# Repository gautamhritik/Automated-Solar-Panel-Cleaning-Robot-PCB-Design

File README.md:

# Automated Solar Panel Cleaning Robot – PCB Design

## Overview
This repository contains the custom PCB design for an Automated Solar Panel Cleaning Robot.  
The PCB integrates power management, motor interfacing, sensor inputs, communication protocols and system protection required for autonomous solar panel cleaning.

This project is intended for academic, prototyping, and learning purposes.

## Key Features
- Battery-powered operation with regulated outputs
- Buck converter for 5 V and 3.3 V rails
- Motor driver interface for the cleaning mechanism
- Sensor input support (0–3.3 V range)
- Power switch and LED status indication
- Reverse polarity, overcurrent, and transient protection
- Debug and expansion headers

## PCB Specifications
- Design Tool: KiCad
- PCB Layers: 2
- Input Power: Battery / External DC supply
- Logic Levels: 3.3 V, 5 V
- Design Status: Prototype (ERC & DRC verified)
- 
## Usage
1. Open schematic and PCB files using KiCad
2. Review power paths, connectors, and component ratings
3. Modify the design if required
4. Generate Gerber files for fabrication
5. Assemble and test the PCB

## Limitations
- Prototype and academic use only
- Not weatherproof or industrially certified
- Requires enclosure for real-world deployment

## Future Improvements
- EMI and noise optimization
- Battery monitoring and protection enhancement
- Waterproof connectors and enclosure
- Firmware-based diagnostics

## License
MIT License

## Author
Hritik Gautam

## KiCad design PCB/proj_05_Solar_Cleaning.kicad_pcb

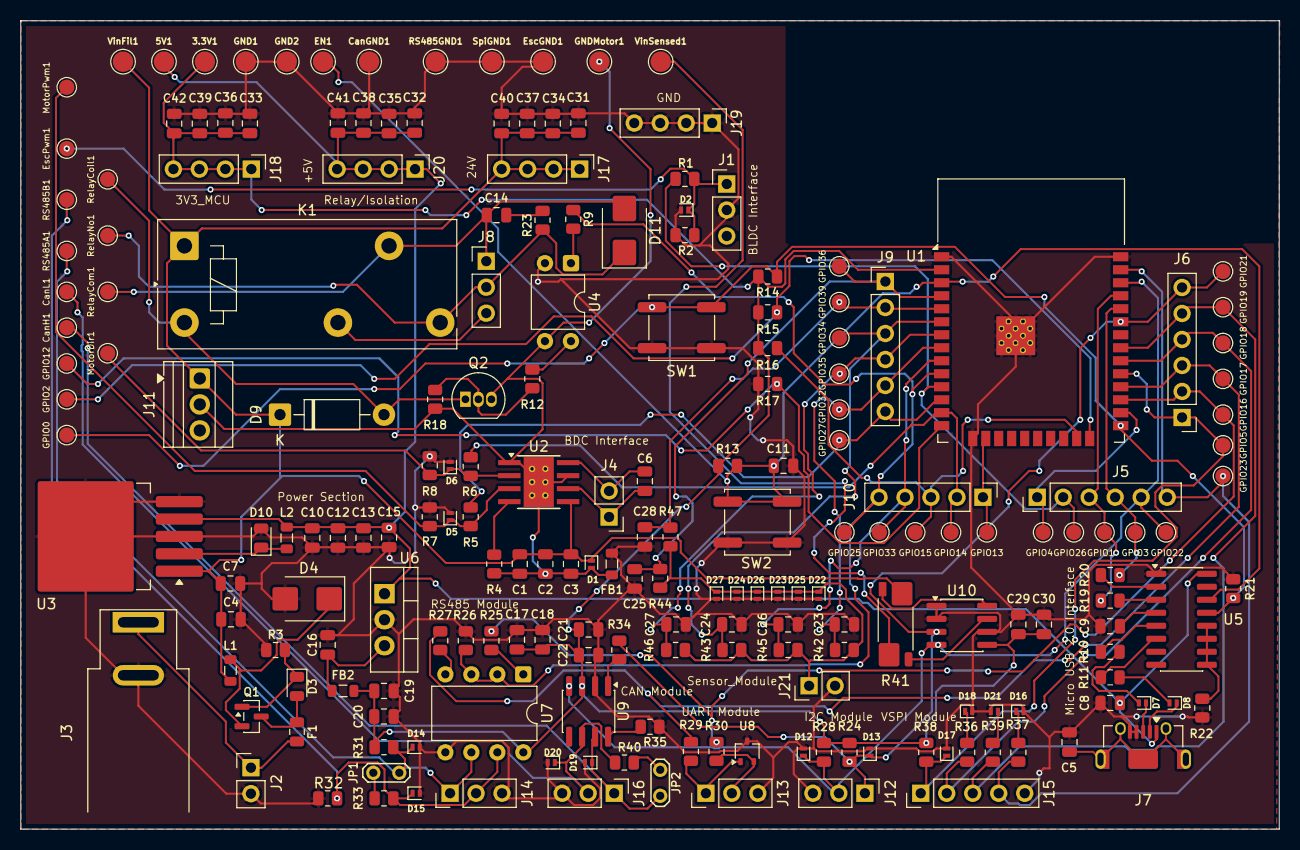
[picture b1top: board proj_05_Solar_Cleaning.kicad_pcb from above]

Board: 2 copper layers, 123.0 x 79.0 mm, 207 parts (0 on the bottom side), 82 nets.

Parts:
3.3V1, 5V1: TestPoint; TestPoint_Pad_D2.0mm
C1: 500µF; C_0805_2012Metric
C2, C5, C6, C9, C11, C13, C17, C20, C21, C23, C24, C25, C26, C27, C28, C29, C37, C38, C39, C40, C41, C42: 0.1µF; C_0805_2012Metric
C3, C12, C18, C19, C22, C30, C34, C35, C36: 1µF; C_0805_2012Metric
C4: C; C_0805_2012Metric
C7, C10: 100µF; C_0805_2012Metric
C8, C15, C31, C32, C33: 10µF; C_0805_2012Metric
C14: 100nF; C_0805_2012Metric
C16: 22µF; C_0805_2012Metric
CanGND1: TestPoint; TestPoint_Pad_D2.0mm
CanH1: TestPoint; TestPoint_Pad_D1.5mm
CanL1: TestPoint; TestPoint_Pad_D1.5mm
D1, D2, D5, D6, D7, D8, D12, D13, D14, D15, D16, D17, D18, D19, D20, D21, D22, D23, D24, D25, D26, D27: PESD5V0L1UL; D_SOD-882
D3: D_Zener; D_0805_2012Metric
D4, D11: D_TVS; D_SMB
D9: 1N4007; D_DO-41_SOD81_P10.16mm_Horizontal
D10: D_Schottky; D_0805_2012Metric
EN1: TestPoint; TestPoint_Pad_D2.0mm
EscGND1: TestPoint; TestPoint_Pad_D2.0mm
EscPwm1: TestPoint; TestPoint_Pad_D1.5mm
F1: Fuse; Fuse_0805_2012Metric
FB1, FB2: FerriteBead; L_0805_2012Metric
GND1, GND2: TestPoint; TestPoint_Pad_D2.0mm
GNDMotor1: TestPoint; TestPoint_Pad_D2.0mm
GPIO0, GPIO1, GPIO2, GPIO3, GPIO4, GPIO5, GPIO12, GPIO13, GPIO14, GPIO15, GPIO16, GPIO17, GPIO18, GPIO19, GPIO21, GPIO22, GPIO23, GPIO25, GPIO26, GPIO27, GPIO32, GPIO33, GPIO34, GPIO35, GPIO36, GPIO39: TestPoint; TestPoint_Pad_D1.5mm
J1, J8, J12, J13, J14, J16: Conn_01x03_Pin; PinHeader_1x03_P2.54mm_Vertical
J2, J4, J21: Conn_01x02_Pin; PinHeader_1x02_P2.54mm_Vertical
J3: Jack-DC; BarrelJack_SwitchcraftConxall_RAPC10U_Horizontal
J5, J6, J9: Conn_01x06_Pin; PinHeader_1x06_P2.54mm_Vertical
J7: USB_B_Micro; USB_Micro-AB_Molex_47590-0001
J10, J15: Conn_01x05_Pin; PinHeader_1x05_P2.54mm_Vertical
J11: Screw_Terminal_01x03; TerminalBlock_Xinya_XY308-2.54-3P_1x03_P2.54mm_Horizontal
J17, J18, J19, J20: Conn_01x04_Pin; PinHeader_1x04_P2.54mm_Vertical
JP1, JP2: Jumper_2_Open; TestPoint_2Pads_Pitch2.54mm_Drill0.8mm
K1: Relay_SPDT; Relay_SPDT_Finder_40.51
L1: L; L_0805_2012Metric
L2: 47µH; L_0805_2012Metric
MotorDir1: TestPoint; TestPoint_Pad_D1.5mm
MotorPwm1: TestPoint; TestPoint_Pad_D1.5mm
Q1: Q_PMOS_GDS; SOT-23
Q2: BC337; TO-92_Inline
R1, R5, R6, R19, R20, R23: 100; R_0805_2012Metric
R2, R7, R8: 100K; R_0805_2012Metric
R3, R13, R14, R15, R16, R17, R18, R21, R22, R26, R35: 10K; R_0805_2012Metric
R4: 22K; R_0805_2012Metric
R9, R31, R32: 680; R_0805_2012Metric
R10, R11: 22; R_0805_2012Metric
R12, R42, R43, R44, R45, R46, R47: 1K; R_0805_2012Metric
R24, R28: 4.7K; R_0805_2012Metric
R25, R27, R29, R30, R34: 33; R_0805_2012Metric
R33, R40: 120; R_0805_2012Metric
R36, R37, R39: 47; R_0805_2012Metric
R38: 47K; R_0805_2012Metric
R41: R_Shunt = 5 mΩ, ≥2 W, 2512package; R_Shunt_Vishay_WSK2512_6332Metric_T1.19mm
RS485A1, RS485B1: TestPoint; TestPoint_Pad_D1.5mm
RS485GND1: TestPoint; TestPoint_Pad_D2.0mm
RelayCoil1: TestPoint; TestPoint_Pad_D1.5mm
RelayCom1: TestPoint; TestPoint_Pad_D1.5mm
RelayNo1: TestPoint; TestPoint_Pad_D1.5mm
SW1, SW2: SW_Push; SW_Push_1P1T_NO_CK_KSC7xxJ
SpiGND1: TestPoint; TestPoint_Pad_D2.0mm
U1: ESP32-WROOM-32D
U2: DRV8871DDA; Texas_HTSOP-8-1EP_3.9x4.9mm_P1.27mm_EP2.95x4.9mm_Mask2.4x3.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
U3: LM2596S-5; TO-263-5_TabPin3
U4: PC817; DIP-4_W7.62mm
U5: CH340C; SOIC-16_3.9x9.9mm_P1.27mm
U6: MCP1825S; TO-220-3_Vertical
U7: MAX3485; DIP-8_W7.62mm
U8: TPD2E2U06DCK; SOT-323_SC-70
U9: SN65HVD230; SOIC-8_3.9x4.9mm_P1.27mm
U10: INA219AxD; SOIC-8_3.9x4.9mm_P1.27mm
VinFil1: TestPoint; TestPoint_Pad_D2.0mm
VinSensed1: TestPoint; TestPoint_Pad_D2.0mm

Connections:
/3V3: C16.1, FB2.1, U6.3 (VO)
/3V3_MCU: 3.3V1.1, C17.1, C18.1, C19.1, C20.1, C21.1, C22.1, C29.1, C30.1, C33.1, C36.1, C39.1, C42.1, FB2.2, J18.1, J18.2, J18.3, J18.4, R13.1, R14.2, R15.2, R16.2, R24.1, R28.1, R31.2, R38.2, U1.2 (VDD), U7.8 (VCC), U9.3 (VCC), U10.5 (VS)
/+5V: 5V1.1, C8.1, C10.1, C12.1, C13.1, C15.1, C32.1, C35.1, C38.1, C41.1, J7.1 (VBUS), J20.1, J20.2, J20.3, J20.4, L2.2, U3.4 (FB), U5.16 (VCC), U6.1 (VI)
/CANH: CanH1.1, D19.1 (K), J16.1, JP2.1 (A), U9.7 (CANH)
/CANL: CanL1.1, D20.1 (K), J16.2, R40.1, U9.6 (CANL)
/EN: C11.1, EN1.1, R13.2, SW2.2, U1.3 (EN), U5.14 (~RTS)
/ESC_PWM_OUT: D2.1 (K), EscPwm1.1, J1.1, R1.2, R2.2
/GND_MOTOR: C1.2, C2.2, C3.2, D1.2 (A), FB1.1, GNDMotor1.1, J11.2, Q2.3 (E), R4.1, R18.1, U2.1 (GND), U2.7 (GND), U2.9 (GND), U4.3
/GPIO0: GPIO0.1, R14.1, R21.2, SW1.1, U1.25 (IO0), U5.13 (~DTR)
/GPIO1: GPIO1.1, J5.3, R19.1, U1.35 (TXD0/IO1)
/GPIO2: GPIO2.1, R15.1, U1.24 (IO2)
/GPIO3: GPIO3.1, J5.4, R20.2, U1.34 (RXD0/IO3)
/GPIO4/RS: GPIO4.1, J5.1, U1.26 (IO4)
/GPIO12: GPIO12.1, R17.1, U1.14 (IO12)
/GPIO13: GPIO13.1, J10.1, U1.16 (IO13)
/GPIO14: GPIO14.1, J10.2, R6.1, U1.13 (IO14)
/GPIO15: GPIO15.1, J10.3, R16.1, U1.23 (IO15)
/GPIO16: GPIO16.1, J6.2, R25.1, R30.2, U1.27 (IO16)
/GPIO17: GPIO17.1, J6.3, R27.1, R29.2, U1.28 (IO17)
/GPIO21: D13.1 (K), GPIO21.1, J6.6, J12.1, R24.2, R34.1, U1.33 (IO21), U10.3 (SDA)
/GPIO22: D12.1 (K), GPIO22.1, J5.5, J12.2, R28.2, U1.36 (IO22), U9.4 (R), U10.4 (SCL)
/GPIO25: GPIO25.1, J10.5, R9.1, R26.2, U1.10 (IO25), U7.2 (~RE), U7.3 (DE)
/GPIO26: GPIO26.1, J5.2, R1.1, U1.11 (IO26)
/GPIO27: GPIO27.1, J9.6, R5.1, U1.12 (IO27)
/GPIO32: C23.1, GPIO32.1, J9.5, R42.1, U1.8 (IO32)
/GPIO33: C26.1, GPIO33.1, J10.4, R45.1, U1.9 (IO33)
/GPIO34: C24.1, GPIO34.1, J9.3, R43.1, U1.6 (IO34)
/GPIO35: C27.1, GPIO35.1, J9.4, R46.1, U1.7 (IO35)
/GPIO36: C25.1, GPIO36.1, J9.1, R44.1, U1.4 (SENSOR_VP)
/GPIO39: C28.1, GPIO39.1, J9.2, R47.1, U1.5 (SENSOR_VN)
/J_Motor Pin 1: C6.2, J4.1, U2.6 (OUT1)
/J_Motor Pin 2: C6.1, J4.2, U2.8 (OUT2)
/MOTOR_DIR: D6.1 (K), MotorDir1.1, R6.2, R8.2, U2.2 (IN2)
/MOTOR_PWM: D5.1 (K), MotorPwm1.1, R5.2, R7.2, U2.3 (IN1)
/RS_A: D14.1 (K), J14.1, JP1.1 (A), R31.1, RS485A1.1, U7.6 (A)
/RS_B: D15.1 (K), J14.2, R32.1, R33.1, RS485B1.1, U7.7 (B)
/Relay_COIL: D9.2 (A), K1.A2, Q2.1 (C), RelayCoil1.1
/Relay_COM: C14.1, D11.2 (A2), J8.1, K1.11, RelayCom1.1
/Relay_NC: J8.3, K1.12
/Relay_NO: D11.1 (A1), J8.2, K1.14, R23.1, RelayNo1.1
/Sensor_Out: D22.1 (K), D23.1 (K), D24.1 (K), D25.1 (K), D26.1 (K), D27.1 (K), J21.1, R42.2, R43.2, R44.2, R45.2, R46.2, R47.2
/USB_D+: D7.2 (A), R10.1
/USB_D-: D8.2 (A), R11.1
/VIN_24V: F1.1, J2.1, J3.1
/VIN_FILTERED: C1.1, C2.1, C3.1, C4.1, C7.1, C31.1, C34.1, C37.1, C40.1, D1.1 (K), D9.1 (K), J11.1, J17.1, J17.2, J17.3, J17.4, K1.A1, L1.2, R41.1, U2.5 (VM), U3.1 (VIN), VinFil1.1
/VIN_Sensed: R41.4, VinSensed1.1
/VSPI_GPIO5_CS: D17.1 (K), GPIO5.1, J6.1, J15.1, R38.1, U1.29 (IO5)
/VSPI_GPIO18_SCLK: GPIO18.1, J6.4, J15.2, R36.1, U1.30 (IO18)
/VSPI_GPIO19_MISO: GPIO19.1, J6.5, J15.3, R39.1, U1.31 (IO19)
/VSPI_GPIO23_MOSI: GPIO23.1, J5.6, J15.4, R37.1, U1.37 (IO23)
GND: C4.2, C5.1, C7.2, C8.2, C9.2, C10.2, C11.2, C12.2, C13.2, C15.2, C16.2, C17.2, C18.2, C19.2, C20.2, C21.2, C22.2, C23.2, C24.2, C25.2, C26.2, C27.2, C28.2, C29.2, C30.2, C31.2, C32.2, C33.2, C34.2, C35.2, C36.2, C37.2, C38.2, C39.2, C40.2, C41.2, C42.2, CanGND1.1, D2.2 (A), D4.2 (A2), D5.2 (A), D6.2 (A), D10.2 (A), D12.2 (A), D13.2 (A), D14.2 (A), D15.2 (A), D16.2 (A), D17.2 (A), D18.2 (A), D19.2 (A), D20.2 (A), D21.2 (A), D22.2 (A), D23.2 (A), D24.2 (A), D25.2 (A), D26.2 (A), D27.2 (A), EscGND1.1, FB1.2, GND1.1, GND2.1, J1.2, J2.2, J3.2, J7.4 (ID), J7.5 (GND), J12.3, J13.3, J14.3, J15.5, J16.3, J19.1, J19.2, J19.3, J19.4, J21.2, R2.1, R3.2, R7.1, R8.1, R17.2, R21.1, R22.1, R26.1, R32.2, R35.1, RS485GND1.1, SW1.2, SW2.1, SpiGND1.1, U1.1 (GND), U1.15 (GND), U1.38 (GND), U1.39 (GND), U3.3 (GND), U3.5 (~ON/OFF), U4.2, U5.1 (GND), U6.2 (GND), U7.5 (GND), U8.3, U9.2 (GND), U10.1 (A1), U10.2 (A0), U10.6 (GND)
unnamed: C14.2, R23.2
unnamed: D3.2 (A), F1.2, Q1.3 (S)
unnamed: D3.1 (K), Q1.1 (G), R3.1
unnamed: D4.1 (A1), L1.1, Q1.2 (D)
unnamed: D7.1 (K), J7.3 (D+)
unnamed: D8.1 (K), J7.2 (D-)
unnamed: D10.1 (K), L2.1, U3.2 (OUT)
unnamed: D16.1 (K), R37.2
unnamed: D18.1 (K), R36.2
unnamed: D21.1 (K), R39.2
unnamed: C5.2, J7.6 (Shield)
unnamed: J13.1, R29.1, U8.1
unnamed: J13.2, R30.1, U8.2
unnamed: JP1.2 (B), R33.2
unnamed: JP2.2 (B), R40.2
unnamed: Q2.2 (B), R12.2, R18.2
unnamed: R9.2, U4.1
unnamed: R12.1, U4.4
unnamed: R4.2, U2.4 (ILIM)
unnamed: R19.2, U5.3 (RXD)
unnamed: R20.1, U5.2 (TXD)
unnamed: R10.2, U5.5 (UD+)
unnamed: R11.2, U5.6 (UD-)
unnamed: C9.1, U5.4 (V3)
unnamed: R22.2, U5.9 (~CTS), U5.10 (~DSR), U5.11 (~RI), U5.12 (~DCD)
unnamed: R27.2, U7.4 (DI)
unnamed: R25.2, U7.1 (RO)
unnamed: R34.2, U9.1 (D)
unnamed: R35.2, U9.8 (Rs)
unnamed: R41.2, U10.8 (IN+)
unnamed: R41.3, U10.7 (IN-)

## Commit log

2026-01-30 Second Commit
2026-01-30 Add README for Automated Solar Panel Cleaning Robot
    Added detailed documentation for the Automated Solar Panel Cleaning Robot PCB design, including features, specifications, usage instructions, limitations, and future improvements.
